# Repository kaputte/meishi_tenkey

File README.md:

# meishi_tenkey

XIAO RP2040 を使用した 5x4 テンキーキーボード

- QMKファームウェア対応
- 2レイヤー（テンキー / ナビゲーション）

## 注意事項

v0.1のPCBではマイコンのスルーホールの間隔を間違えており、Xiaoのピンヘッダより僅かに広いです。先にピンヘッダとマイコンを挿してからハンダ付けしてください。Xiaoのピンヘッダを先に実装するとPCBに挿さらなくなります。

> **v0.2で修正済み。** v0.2以降のPCBではこの問題は解消されています。

## レイアウト

```
┌───┬───┬───┬───┐
│NLk│ / │ * │ - │
├───┼───┼───┼───┤
│ 7 │ 8 │ 9 │ + │
├───┼───┼───┼───┤
│ 4 │ 5 │ 6 │ + │
├───┼───┼───┼───┤
│ 1 │ 2 │ 3 │Ent│
├───┼───┼───┼───┤
│ 0 │Fn │ . │Ent│
└───┴───┴───┴───┘
```

## 部品表

| 部品 | 数量 | 備考 |
|------|------|------|
| XIAO RP2040 | 1 | ピンヘッダで取り付け |
| タクトスイッチ | 20 | 薄型（厚さ約1.5mm） |
| ダイオード（1N4148W） | 20 | |

## ファームウェア

### 書き込み方法

1. XIAO RP2040 の B ボタンを押しながら R ボタンを押す
2. PC にリムーバブルドライブとしてマウントされる
3. `qmk_firmware/meishi_tenkey_default.uf2` をドライブにコピー

### キーマップのカスタマイズ

レイアウトを変更したい場合は、Linux または WSL 上に QMK 環境を構築し、以下の手順で行ってください。

1. `./qmk_firmware/keyboards/meishi_tenkey` を QMK 本体の `keyboards/` 以下にコピー
2. `keymaps/default/keymap.c` を編集
3. `qmk compile -kb meishi_tenkey -km default` でビルド
4. 出力された `.uf2` ファイルを XIAO RP2040 に書き込み

## PCB設計環境

KiCad 9.0.7 で編集しています。

- [Xiao_Kicad_Library](https://github.com/Seeed-Studio/Xiao_Kicad_Library) - XIAO RP2040 のシンボル / フットプリント

## ライセンス

GPL-2.0

ハードウェア部分（KiCad）については、将来的に CERN-OHL-S へ変更する可能性があります。

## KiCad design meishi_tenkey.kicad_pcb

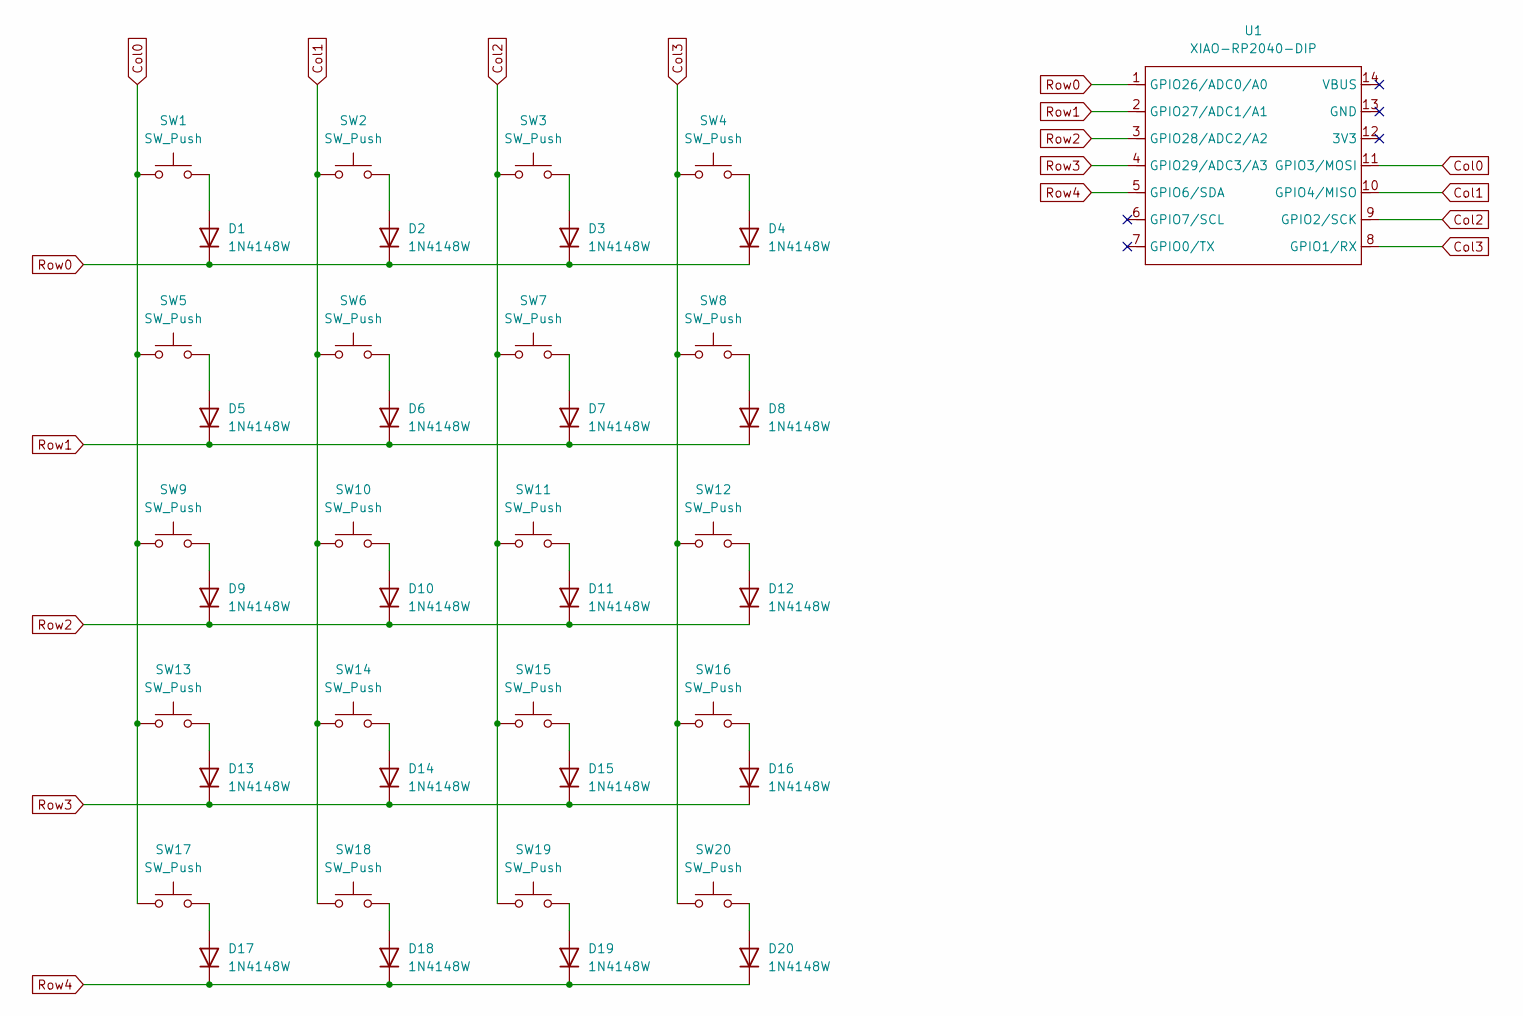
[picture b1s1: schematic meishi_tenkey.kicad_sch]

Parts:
D1, D2, D3, D4, D5, D6, D7, D8, D9, D10, D11, D12, D13, D14, D15, D16, D17, D18, D19, D20: 1N4148W; D_SOD-123
SW1, SW2, SW3, SW4, SW5, SW6, SW7, SW8, SW9, SW10, SW11, SW12, SW13, SW14, SW15, SW16, SW17, SW18, SW19, SW20: SW_Push; SW_SPST_TL3342
U1: XIAO-RP2040-DIP

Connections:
Col0: SW1.1, SW5.1, SW9.1, SW13.1, SW17.1, U1.11 (GPIO3/MOSI)
Col1: SW2.1, SW6.1, SW10.1, SW14.1, SW18.1, U1.10 (GPIO4/MISO)
Col2: SW3.1, SW7.1, SW11.1, SW15.1, SW19.1, U1.9 (GPIO2/SCK)
Col3: SW4.1, SW8.1, SW12.1, SW16.1, SW20.1, U1.8 (GPIO1/RX)
unnamed: D1.2 (A), SW1.2
unnamed: D2.2 (A), SW2.2
unnamed: D3.2 (A), SW3.2
unnamed: D4.2 (A), SW4.2
unnamed: D5.2 (A), SW5.2
unnamed: D6.2 (A), SW6.2
unnamed: D7.2 (A), SW7.2
unnamed: D8.2 (A), SW8.2
unnamed: D9.2 (A), SW9.2
unnamed: D10.2 (A), SW10.2
unnamed: D11.2 (A), SW11.2
unnamed: D12.2 (A), SW12.2
unnamed: D13.2 (A), SW13.2
unnamed: D14.2 (A), SW14.2
unnamed: D15.2 (A), SW15.2
unnamed: D16.2 (A), SW16.2
unnamed: D17.2 (A), SW17.2
unnamed: D18.2 (A), SW18.2
unnamed: D19.2 (A), SW19.2
unnamed: D20.2 (A), SW20.2
Row0: D1.1 (K), D2.1 (K), D3.1 (K), D4.1 (K), U1.1 (GPIO26/ADC0/A0)
Row1: D5.1 (K), D6.1 (K), D7.1 (K), D8.1 (K), U1.2 (GPIO27/ADC1/A1)
Row2: D9.1 (K), D10.1 (K), D11.1 (K), D12.1 (K), U1.3 (GPIO28/ADC2/A2)
Row3: D13.1 (K), D14.1 (K), D15.1 (K), D16.1 (K), U1.4 (GPIO29/ADC3/A3)
Row4: D17.1 (K), D18.1 (K), D19.1 (K), D20.1 (K), U1.5 (GPIO6/SDA)

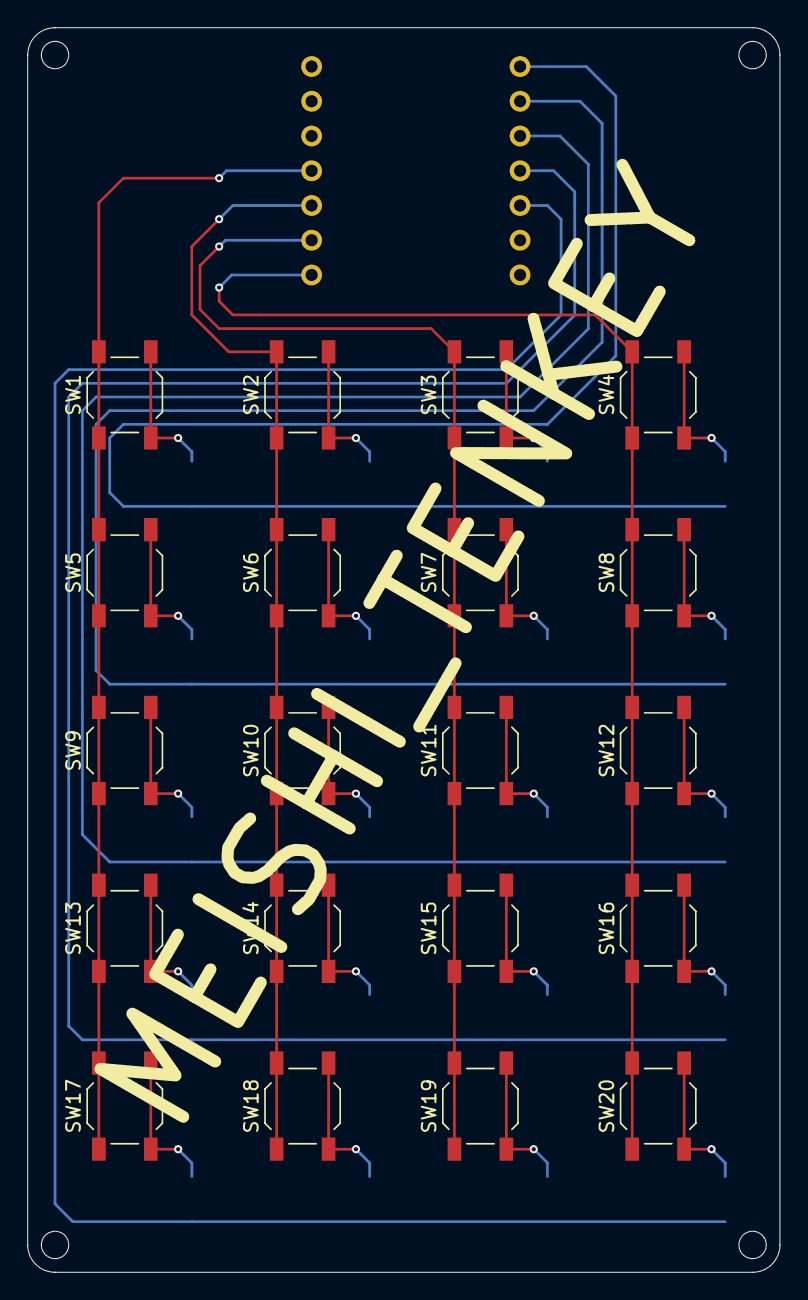
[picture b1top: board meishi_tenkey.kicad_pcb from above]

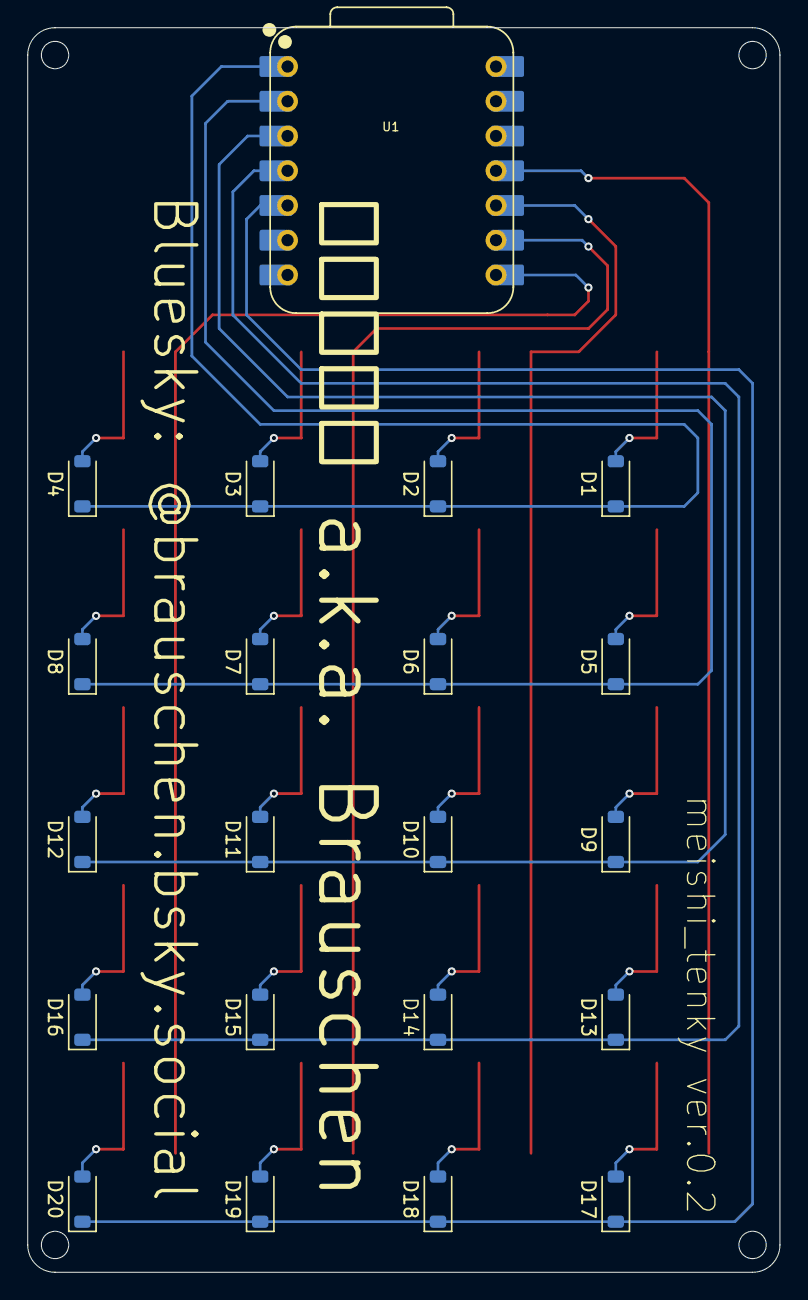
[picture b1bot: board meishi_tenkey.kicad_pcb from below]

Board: 2 copper layers, 55.0 x 91.0 mm, 41 parts (21 on the bottom side), 29 nets.

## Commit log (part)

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2026-02-08 README.md の更新
2026-02-27 Update .gitignore for directory of Autodesk Fusion.
